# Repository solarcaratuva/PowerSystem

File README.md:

View this project on [CADLAB.io](https://cadlab.io/project/23149). 

# PowerSystem
Developing PCB for Power System and ECU code for STM32F413ZH.

## PCB Design
TODO:
1) ~Remove double throw 12V power relay off PCB (as it is chasis mount)~
2) ~Add charge and discharge relays to PCB~
3) ~Figure out which pins on the STM to use for what~
4) ~Add extra CAN port (need one for Rx from BMS, and one for Tx and Rx to other PCBs) as well as the external CAN Tranceivers~
5) ~Make sure everything has footprint and 3d model~
6) Pick out exact voltage regulator models
7) Layout board

## STM 32 & ECU Code
TODO:
1) Figure out which pins on the STM to use for what
2) Figure out what each power supply input (VDD, VSS, VBAT, VDDUSB, VDDA, VSSA) and other important inputs are for 

Pin Names used by MbedOS:
https://os.mbed.com/platforms/ST-Nucleo-F413ZH/

Important pins for us:

| STM Pin Name | MbedOS Pin Name(s) | Function |
| :---: | :---: | :--- |
| PB0 | `PB_0`/`LED1` | BMS Error |
| PB7 | `PB_7`/`LED2` | CAN Error |
| PB14 | `PB_14`/`LED3` | Unused LED |
| PC13 | `PC_13`/`BUTTON1` | Unused Button |
| PD0 | `PD_0` | CAN1 (BMS) Receivier |
| PD1 | `PD_1` | CAN1 (BMS) Transmitter |
| PB12 | `PB_12` | CAN2 (Main) Receivier |
| PB13 | `PB_13` | CAN2 (Main) Transmitter |
| PG9 | `PG_9`/`D0` | DC-DC ON |
| PG14 | `PG_14`/`D1` | Unused Digital I/O |
| PF15 | `PF_15`/`D2` | Unused Digital I/O |
| PE13 | `PE_13`/`D3` | Unused Digital I/O |
| PF14 | `PF_14`/`D4` | Unused Digital I/O |
| PE11 | `PE_11`/`D5` | Unused Digital I/O |
| PE9 | `PE_9`/`D6` | Unused Digital I/O |
| PF13 | `PF_13`/`D7` | Unused Digital I/O |
| PF12 | `PF_12`/`D8` | Unused Digital I/O |
| PD15 | `PD_15`/`D9` | Unused Digital I/O |
| PD14 | `PD_14`/`D10` | Unused Digital I/O |
| PA7 | `PA_7`/`D11` | Unused Digital I/O |
| PA6 | `PA_6`/`D12` | Unused Digital I/O |
| PA5 | `PA_5`/`D13` | Unused Digital I/O |
| PB9 | `PB_9`/`D14` | Unused Digital I/O |
| PB8 | `PB_8`/`D15` | Unused Digital I/O |
| PA3 | `PA_3`/`A0` | AUX Voltage |
| PC0 | `PC_0`/`A1` | DC-DC Voltage |
| PC3 | `PC_3`/`A2` | Unused Analog I/O |
| PC1 | `PC_1`/`A3` | Unused Analog I/O |
| PC4 | `PC_4`/`A4` | Unused Analog I/O |
| PC5 | `PC_5`/`A5` | Unused Analog I/O |

Note: the LEDs for Power ON, AUX ON, DC-DC ON, and AUX/DC-DC being used can be directly connected to the power supply / relay driving it.

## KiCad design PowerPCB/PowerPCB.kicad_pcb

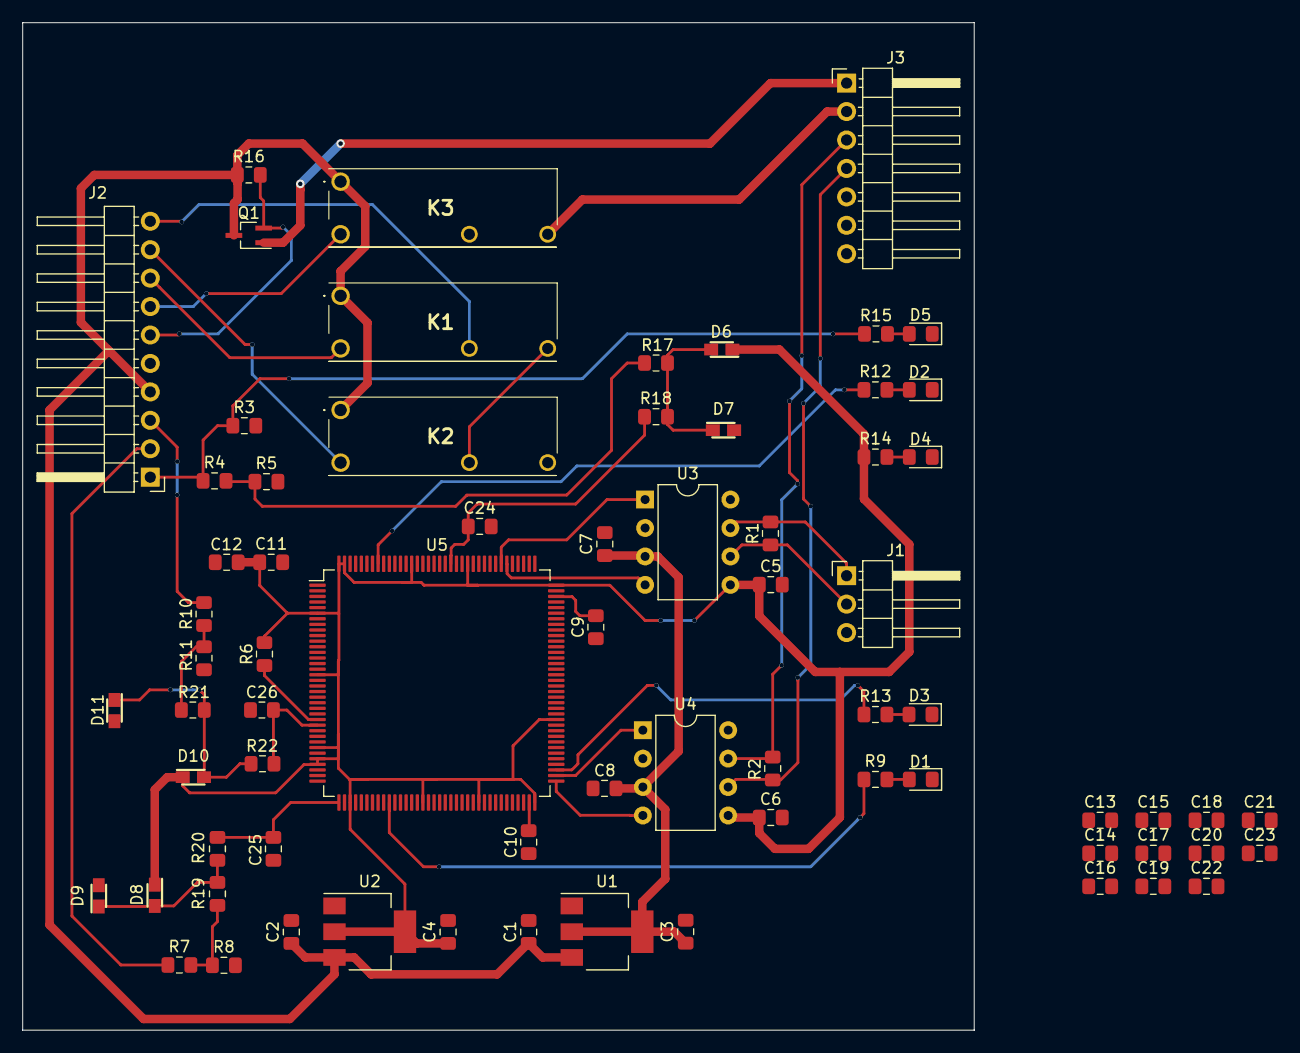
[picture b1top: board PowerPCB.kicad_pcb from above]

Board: 2 copper layers, 85.0 x 90.0 mm, 71 parts (0 on the bottom side), 43 nets.

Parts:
C1, C2, C3, C4, C5, C6, C7, C8: 0.1u; C_0805_2012Metric_Pad1.15x1.40mm_HandSolder
C9, C10: 2.2u; C_0805_2012Metric_Pad1.15x1.40mm_HandSolder
C11, C12, C13, C14, C15, C16, C17, C18, C19, C20, C21, C23: 100n; C_0805_2012Metric_Pad1.15x1.40mm_HandSolder
C22: 4.7u; C_0805_2012Metric_Pad1.15x1.40mm_HandSolder
C24, C25, C26: 0.01u; C_0805_2012Metric_Pad1.15x1.40mm_HandSolder
D1, D2, D3, D4, D5: LED; LED_0805_2012Metric_Pad1.15x1.40mm_HandSolder
D6, D7, D8, D9, D10, D11: SD0805S040S0R1; DIOM2013X100N
J1: Conn_01x03_Male; PinHeader_1x03_P2.54mm_Horizontal
J2: Conn_01x10_Male; PinHeader_1x10_P2.54mm_Horizontal
J3: Conn_01x07_Male; PinHeader_1x07_P2.54mm_Horizontal
K1, K2, K3: 1721081-5; 17210815
Q1: Q_PMOS_DGS; SOT-323_SC-70_Handsoldering
R1, R2: 120; R_0805_2012Metric_Pad1.15x1.40mm_HandSolder
R3, R4, R7, R10, R16: 100k; R_0805_2012Metric_Pad1.15x1.40mm_HandSolder
R5, R8, R11: 33k; R_0805_2012Metric_Pad1.15x1.40mm_HandSolder
R6: 40k; R_0805_2012Metric_Pad1.15x1.40mm_HandSolder
R9, R12, R13, R14, R15: 100; R_0805_2012Metric_Pad1.15x1.40mm_HandSolder
R17, R19, R21: 10; R_0805_2012Metric_Pad1.15x1.40mm_HandSolder
R18, R20, R22: 1k; R_0805_2012Metric_Pad1.15x1.40mm_HandSolder
U1: NCP1117-5.0_SOT223; SOT-223-3_TabPin2
U2: NCP1117-3.3_SOT223; SOT-223-3_TabPin2
U3, U4: MCP2562-E-P; DIP-8_W7.62mm
U5: STM32F413ZHTx; LQFP-144_20x20mm_P0.5mm

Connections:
/Fan/Fan+: J3.1, Q1.1
/Fan/Fan-: J3.2, K3.4
/Fan/FanCtrl: J2.7, K3.2
/Fan/FanPWM: J2.6, Q1.2, R16.2
/InputProtection2/ToSTM: C25.1, R20.1, U5.37
/InputProtection2/Vin: R7.2, R8.1, R19.2
/InputProtection3/ToSTM: C26.1, R22.1, U5.26
/InputProtection3/Vin: R10.2, R11.1, R21.2
/InputProtection/ToSTM: C24.1, R18.1, U5.124
/InputProtection/Vin: R4.2, R5.1, R17.2
AUX+: J2.2, R7.1
BMS_CAN_HI: J1.1, R1.1, U3.7
BMS_CAN_LO: J1.2, R1.2, U3.6
BMS_CAN_RX: U3.4, U5.114
BMS_CAN_TX: U3.1, U5.115
DCDC+: J2.3, R10.1
DCDC_ON: J2.1, R3.1, R4.1, R15.1
GND: C1.2, C2.2, C3.2, C4.2, C5.2, C6.2, C7.2, C8.2, C9.2, C10.2, C11.2, C12.2, C13.2, C14.2, C15.2, C16.2, C17.2, C18.2, C19.2, C20.2, C21.2, C22.2, C23.2, C24.2, C25.2, C26.2, D1.1, D2.1, D3.1, D4.1, D5.1, D7.2, D9.2, D11.2, J1.3, J2.5, K2.4, K3.3, R3.2, R5.2, R8.2, R11.2, U1.1, U2.1, U3.2, U3.8, U4.2, U4.8, U5.16, U5.31, U5.38, U5.51, U5.61, U5.83, U5.94, U5.107, U5.120, U5.130, U5.138
MAIN_CAN_HI: J3.3, R2.1, U4.7
MAIN_CAN_LO: J3.4, R2.2, U4.6
MAIN_CAN_RX: U4.4, U5.73
MAIN_CAN_TX: U4.1, U5.74
unnamed: C9.1, U5.106
unnamed: C10.1, U5.71
unnamed: D1.2, R9.2
unnamed: D2.2, R12.2
unnamed: D3.2, R13.2
unnamed: D4.2, R14.2
unnamed: D5.2, R15.2
unnamed: D6.2, D7.1, R17.1, R18.2
unnamed: D8.2, D9.1, R19.1, R20.2
unnamed: D10.2, D11.1, R21.1, R22.2
unnamed: J2.8, K1.2
unnamed: J2.9, K2.2
unnamed: J2.10, K1.3
unnamed: K1.4, K2.3
unnamed: R6.2, U5.25
unnamed: R9.1, U5.46
unnamed: R12.1, U5.137
unnamed: R13.1, U5.75
VCC_3.3: C4.1, C5.1, C6.1, C11.1, C12.1, C13.1, C14.1, C15.1, C16.1, C17.1, C18.1, C19.1, C20.1, C21.1, C22.1, C23.1, D6.1, D8.1, D10.1, R6.1, R14.1, U2.2, U3.5, U4.5, U5.6, U5.17, U5.30, U5.32, U5.33, U5.39, U5.52, U5.62, U5.72, U5.84, U5.95, U5.108, U5.121, U5.131, U5.143, U5.144
VCC_5: C3.1, C7.1, C8.1, U1.2, U3.3, U4.3
VCC_12: C1.1, C2.1, J2.4, K1.1, K2.1, K3.1, Q1.3, R16.1, U1.3, U2.3

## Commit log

2020-04-05 Initial Power PCB
2020-04-05 Testing Readme change
2020-04-05 Power PCB connector
2020-04-12 Added inital components
2020-04-12 Added Fan Components
2020-04-12 Added Fan Testing Circuit
2020-04-12 created PlatformIO project
2020-04-16 more fan changes
2020-04-16 Added test PCB to test simulator
2020-04-19 Added Multisim File for testing Fan Circuitry and MOSFET spice models
2020-04-26 Added Voltage Divider to PowerPCB for stepping down AUX voltage before outputting it to STM
2020-05-02 added fan system
2020-05-03 Added Multisim file to test input protection circuitry suggested by Digikey
2020-05-11 moved protection circuit into KiCad
2020-05-11 made all paths to spice models relative and renumbered pins of MOSFETs in Fan
2020-05-11 Cleaned up Fan Schematic
2020-05-11 Made all file paths use forward slashes
2020-05-11 Changed spice model for p-channel mosfet
2020-05-17 Added Fan circuit as hierarchical block to main PCB
2020-05-24 new relay added to PowerPCB, and its 3D model is added to the library
2020-05-24 added SamacSys Folder, project level footprint references in powerPCB
2020-05-24 reorganizing files for generic directory name
2020-05-24 Added footprints for all components
2020-05-24 Imported components to PCBnew
2020-05-24 added code to test CAN within one MCU
2020-05-29 Added TODO list and STM Pin Names Table to Readme
2020-05-29 Added 3A SPST relays for all relays
2020-05-30 Removed SPDT chassis mount relay, added diode footprint
2020-05-30 Added Charge and Discharge relays
2020-05-31 Removed power diode (will be external) and unnecessary grounds
2020-05-31 Used Strikethrough for TODO list in Readme
2020-05-31 Cleaned up main schematic and corrected text for fan relay
2020-05-31 Added CAN connections to STM
2020-05-31 Added LED connections to STM
2020-05-31 Added AUX+ and DCDC+ as analog inputs
2020-05-31 Finished connections to STM, exported to PCBnew
2020-06-06 wrote code to test CAN and added build cache to speed up build time
2020-06-07 Placed all components in PCB layout
2020-06-07 Testing branch
2020-06-07 Create new Daichi branch, made PCB layout up to the tracks
2020-06-11 Added input protection circuitry as sub-schematic
2020-06-11 Added footprints for resistors and capacitors
2020-06-13 Changed Shottky diodes to 0805 size
2020-06-13 moved all PowerCode into separate repo
2020-06-14 small changes to tracks
2020-06-14 Added bypass capacitors to CAN transceivers
2020-06-14 Changed Shottky diode footprint to read text better
2020-06-14 cleared up rats nest more and keep LEDs together
2020-06-14 Moved text of Shottky diodes so it is readable
2020-06-14 UPdated PCB with protection
2020-06-14 Imported input protection components to PCBnew
2020-06-14 diode labels look nicer
2020-06-20 Edited footprint of Shottky diodes to have smaller font sizes
2020-06-21 Placed all input protection circuitry components in PCBnew
2020-06-21 organizing PCB layout
2020-06-21 text changes and organization PCB
2020-06-21 Added .gitignore for ignoring auto generated files
2020-06-21 edge cut
2020-06-22 Added edge cuts
2020-06-22 Routed all of VCC_12
2020-06-22 Routed most of Fan circuitry
2020-06-22 Routed 30 mils GND traces
2020-06-22 Routed linear regulators and most of the CAN transceivers
2020-06-22 Routed most of the connections to the STM
2020-06-22 Routed everything except for internal STM connnections
2020-06-23 Finished routing board
2020-06-28 Finished Layout of parts on PCB
2020-07-11 Moved right output connector down to make room for drill hole in corners
2020-07-12 tracks and ground plane draft 1 done
2020-07-13 Added VDD bypass capacitors and values for all components
2020-07-19 Added pull-down resistors to usused pins
2020-07-19 tracks on PCB
2020-07-25 Backlink to CADLAB.io has been added.
2020-07-26 Revert "Backlink to CADLAB.io has been added."
    This reverts commit 8db835b35eb90eabe61308a3852a6d49ed3f350c.
2020-08-02 moved pcb to middle of page
